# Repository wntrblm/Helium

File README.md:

# Winterbloom Helium

Helium is a precision buffered multiple and precision adder for Eurorack.

More details available at https://winterbloom.com/shop/helium

## Repository layout

This repository contains the hardware design files and user guide for Helium:

- **hardware/** contains the hardware design files for the mainboard and blank panel. These are all created using KiCAD.
- **user_guide/** contains the user's guide source files. These are written in Markdown and published using MkDocs.

## License and contributing

Helium is open-source hardware and software, however, licensing a project like this is a little complicated. Please take a chance to review the [LICENSE](LICENSE.md) file.

We welcome contributions! Please read our [Code of Conduct](CODE_OF_CONDUCT.md) first.

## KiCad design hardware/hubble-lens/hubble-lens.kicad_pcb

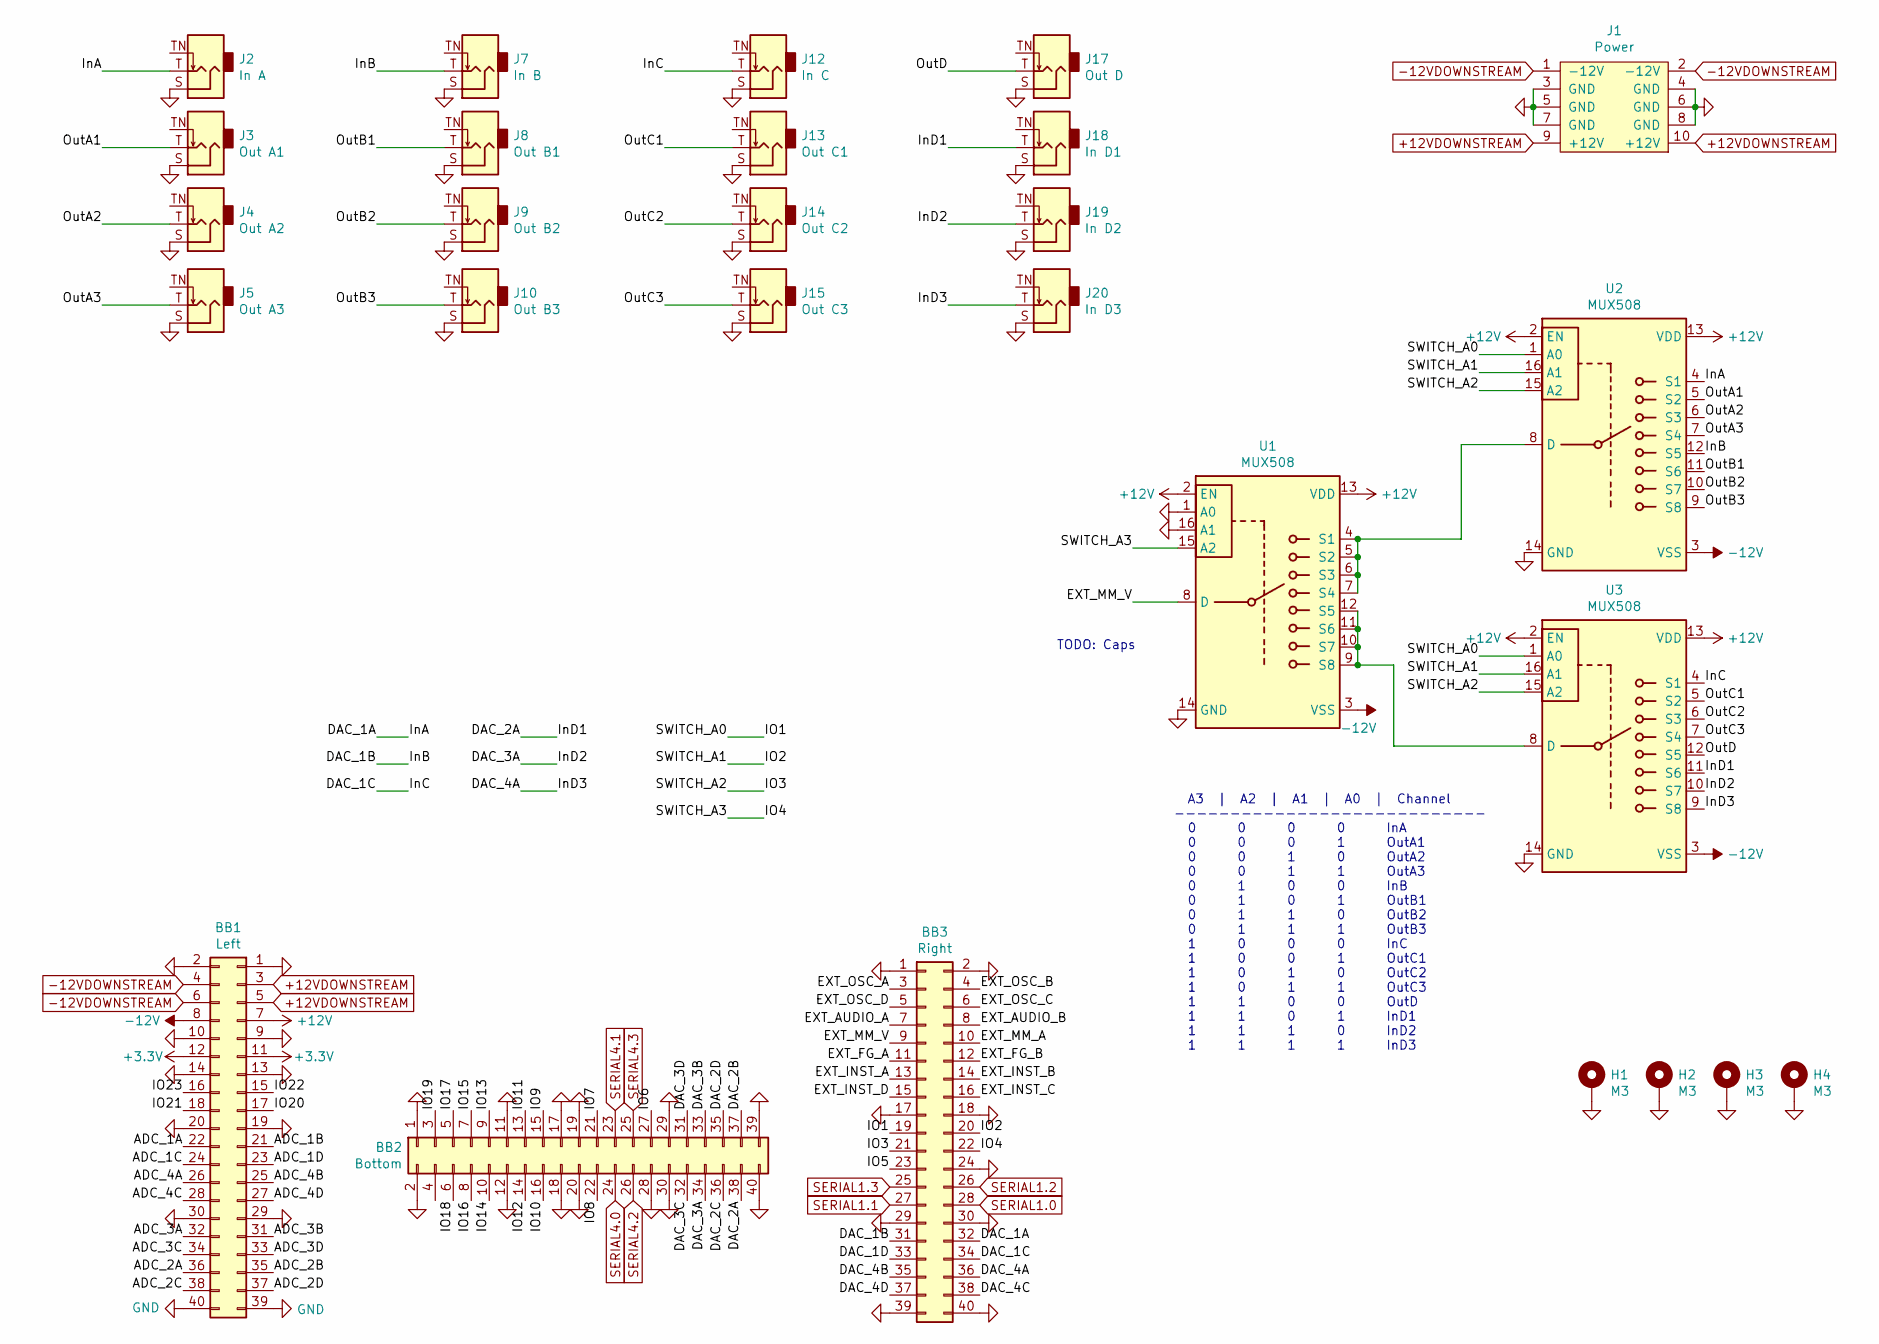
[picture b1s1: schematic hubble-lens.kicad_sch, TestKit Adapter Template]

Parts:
BB1: Left; PinSocket_2x20_P2.54mm_Vertical
BB2: Bottom; PinSocket_2x20_P2.54mm_Vertical
BB3: Right; PinSocket_2x20_P2.54mm_Vertical
H1, H2, H3, H4: M3; MountingHole_3.2mm_M3_Pad_Via
J1: Power; Eurorack_Power; mpn 302-S101
J2: In A; WQP-WQP518MA-skinny; mpn WQP-WQP518MA
J3: Out A1; WQP-WQP518MA-skinny; mpn WQP-WQP518MA
J4: Out A2; WQP-WQP518MA-skinny; mpn WQP-WQP518MA
J5: Out A3; WQP-WQP518MA-skinny; mpn WQP-WQP518MA
J7: In B; WQP-WQP518MA-skinny; mpn WQP-WQP518MA
J8: Out B1; WQP-WQP518MA-skinny; mpn WQP-WQP518MA
J9: Out B2; WQP-WQP518MA-skinny; mpn WQP-WQP518MA
J10: Out B3; WQP-WQP518MA-skinny; mpn WQP-WQP518MA
J12: In C; WQP-WQP518MA-skinny; mpn WQP-WQP518MA
J13: Out C1; WQP-WQP518MA-skinny; mpn WQP-WQP518MA
J14: Out C2; WQP-WQP518MA-skinny; mpn WQP-WQP518MA
J15: Out C3; WQP-WQP518MA-skinny; mpn WQP-WQP518MA
J17: Out D; WQP-WQP518MA-skinny; mpn WQP-WQP518MA
J18: In D1; WQP-WQP518MA-skinny; mpn WQP-WQP518MA
J19: In D2; WQP-WQP518MA-skinny; mpn WQP-WQP518MA
J20: In D3; WQP-WQP518MA-skinny; mpn WQP-WQP518MA
U1, U2, U3: MUX508; TSSOP-16_4.4x5mm_P0.65mm

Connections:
+3V3: BB1.11, BB1.12
+12V: BB1.7, U1.2 (EN), U1.13 (VDD), U2.2 (EN), U2.13 (VDD), U3.2 (EN), U3.13 (VDD)
+12VDOWNSTREAM: BB1.3, BB1.5, J1.9 (+12V), J1.10 (+12V)
-12V: BB1.8, U1.3 (VSS), U2.3 (VSS), U3.3 (VSS)
-12VDOWNSTREAM: BB1.4, BB1.6, J1.1 (-12V), J1.2 (-12V)
/ADC_1A: BB1.22
/ADC_1B: BB1.21
/ADC_1C: BB1.24
/ADC_1D: BB1.23
/ADC_2A: BB1.36
/ADC_2B: BB1.35
/ADC_2C: BB1.38
/ADC_2D: BB1.37
/ADC_3A: BB1.32
/ADC_3B: BB1.31
/ADC_3C: BB1.34
/ADC_3D: BB1.33
/ADC_4A: BB1.26
/ADC_4B: BB1.25
/ADC_4C: BB1.28
/ADC_4D: BB1.27
/DAC_1A: BB3.32, J2.T (Tip), U2.4 (S1)
/DAC_1B: BB3.31, J7.T (Tip), U2.12 (S5)
/DAC_1C: BB3.34, J12.T (Tip), U3.4 (S1)
/DAC_1D: BB3.33
/DAC_2A: BB2.38, J18.T (Tip), U3.11 (S6)
/DAC_2B: BB2.37
/DAC_2C: BB2.36
/DAC_2D: BB2.35
/DAC_3A: BB2.34, J19.T (Tip), U3.10 (S7)
/DAC_3B: BB2.33
/DAC_3C: BB2.32
/DAC_3D: BB2.31
/DAC_4A: BB3.36, J20.T (Tip), U3.9 (S8)
/DAC_4B: BB3.35
/DAC_4C: BB3.38
/DAC_4D: BB3.37
/EXT_AUDIO_A: BB3.7
/EXT_AUDIO_B: BB3.8
/EXT_FG_A: BB3.11
/EXT_FG_B: BB3.12
/EXT_INST_A: BB3.13
/EXT_INST_B: BB3.14
/EXT_INST_C: BB3.16
/EXT_INST_D: BB3.15
/EXT_MM_A: BB3.10
/EXT_MM_V: BB3.9, U1.8 (D)
/EXT_OSC_A: BB3.3
/EXT_OSC_B: BB3.4
/EXT_OSC_C: BB3.6
/EXT_OSC_D: BB3.5
/IO1: BB3.19, U2.1 (A0), U3.1 (A0)
/IO2: BB3.20, U2.16 (A1), U3.16 (A1)
/IO3: BB3.21, U2.15 (A2), U3.15 (A2)
/IO4: BB3.22, U1.15 (A2)
/IO5: BB3.23
/IO6: BB2.27
/IO7: BB2.21
/IO8: BB2.22
/IO9: BB2.15
/IO10: BB2.16
/IO11: BB2.13
/IO12: BB2.14
/IO13: BB2.9
/IO14: BB2.10
/IO15: BB2.7
/IO16: BB2.8
/IO17: BB2.5
/IO18: BB2.6
/IO19: BB2.3
/IO20: BB1.17
/IO21: BB1.18
/IO22: BB1.15
/IO23: BB1.16
/OutA1: J3.T (Tip), U2.5 (S2)
/OutA2: J4.T (Tip), U2.6 (S3)
/OutA3: J5.T (Tip), U2.7 (S4)
/OutB1: J8.T (Tip), U2.11 (S6)
/OutB2: J9.T (Tip), U2.10 (S7)
/OutB3: J10.T (Tip), U2.9 (S8)
/OutC1: J13.T (Tip), U3.5 (S2)
/OutC2: J14.T (Tip), U3.6 (S3)
/OutC3: J15.T (Tip), U3.7 (S4)
/OutD: J17.T (Tip), U3.12 (S5)
GND: BB1.1, BB1.2, BB1.9, BB1.10, BB1.13, BB1.14, BB1.19, BB1.20, BB1.29, BB1.30, BB1.39, BB1.40, BB2.1, BB2.2, BB2.11, BB2.12, BB2.17, BB2.18, BB2.19, BB2.20, BB2.28, BB2.29, BB2.30, BB2.39, BB2.40, BB3.1, BB3.2, BB3.17, BB3.18, BB3.24, BB3.29, BB3.30, BB3.39, BB3.40, H1.1, H2.1, H3.1, H4.1, J1.3 (GND), J1.4 (GND), J1.5 (GND), J1.6 (GND), J1.7 (GND), J1.8 (GND), J2.S (Sleeve), J3.S (Sleeve), J4.S (Sleeve), J5.S (Sleeve), J7.S (Sleeve), J8.S (Sleeve), J9.S (Sleeve), J10.S (Sleeve), J12.S (Sleeve), J13.S (Sleeve), J14.S (Sleeve), J15.S (Sleeve), J17.S (Sleeve), J18.S (Sleeve), J19.S (Sleeve), J20.S (Sleeve), U1.1 (A0), U1.14 (GND), U1.16 (A1), U2.14 (GND), U3.14 (GND)
unnamed: U1.4 (S1), U1.5 (S2), U1.6 (S3), U1.7 (S4), U2.8 (D)
unnamed: U1.9 (S8), U1.10 (S7), U1.11 (S6), U1.12 (S5), U3.8 (D)
SERIAL1.0: BB3.28
SERIAL1.1: BB3.27
SERIAL1.2: BB3.26
SERIAL1.3: BB3.25
SERIAL4.0: BB2.24
SERIAL4.1: BB2.23
SERIAL4.2: BB2.26
SERIAL4.3: BB2.25

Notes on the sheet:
A3 | A2 | A1 | A0 | Channel ---------------------------- 0 0 0 0 InA 0 0 0 1 OutA1 0 0 1 0 OutA2 0 0 1 1 OutA3 0 1 0 0 InB 0 1 0 1 OutB1 0 1 1 0 OutB2 0 1 1 1 OutB3 1 0 0 0 InC 1 0 0 1 OutC1 1 0 1 0 OutC2 1 0 1 1 OutC3 1 1 0 0 OutD 1 1 0 1 InD1 1 1 1 0 InD2 1 1 1 1 InD3
TODO: Caps

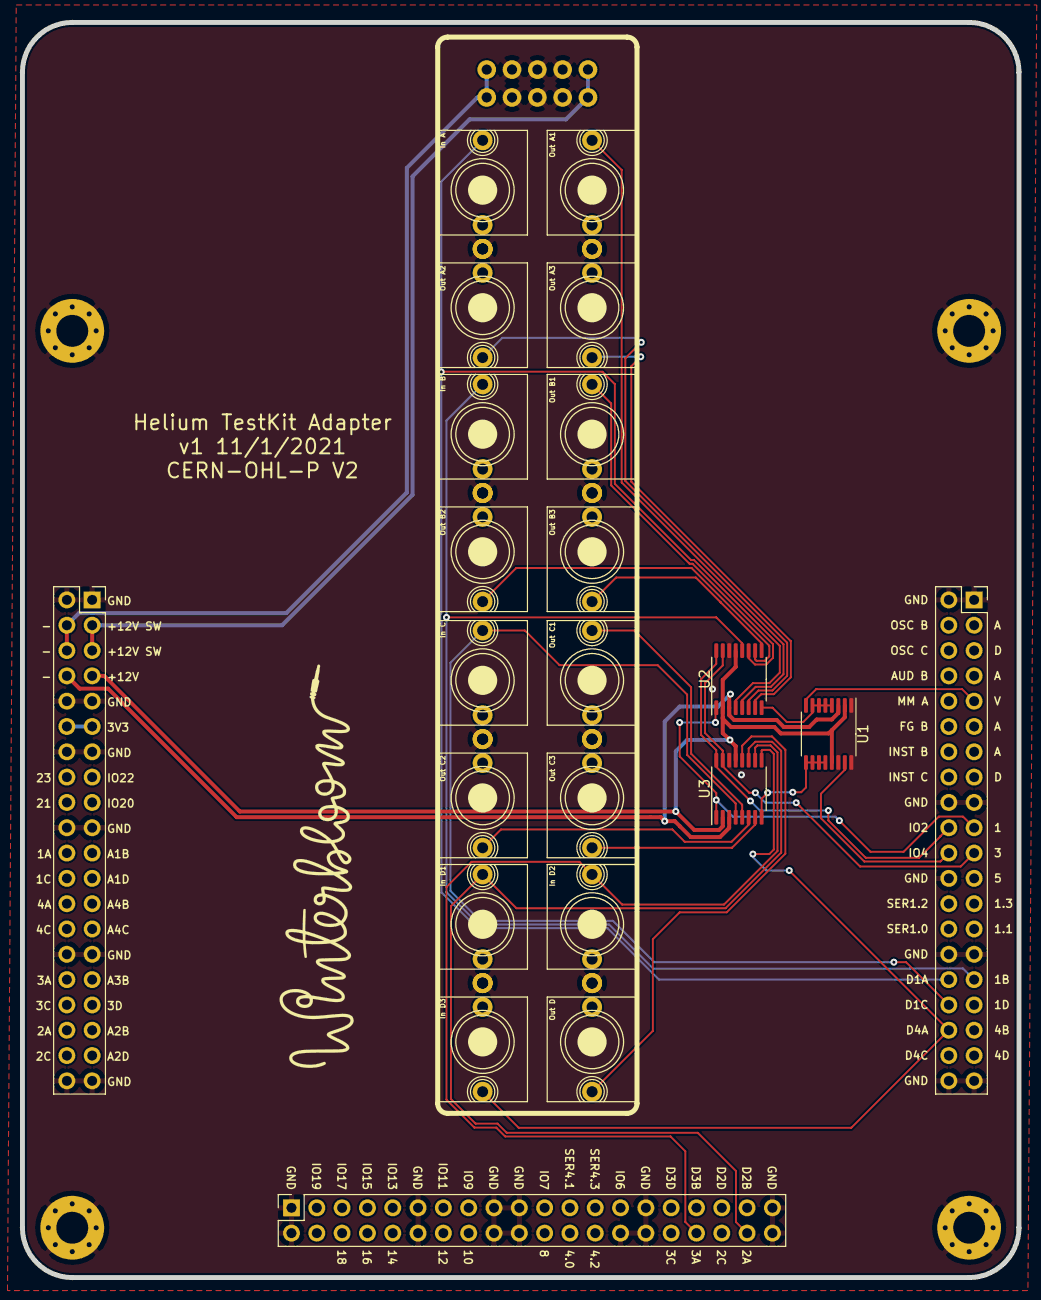
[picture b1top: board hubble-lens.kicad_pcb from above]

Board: 2 copper layers, 100.0 x 126.0 mm, 27 parts (1 on the bottom side), 29 nets.

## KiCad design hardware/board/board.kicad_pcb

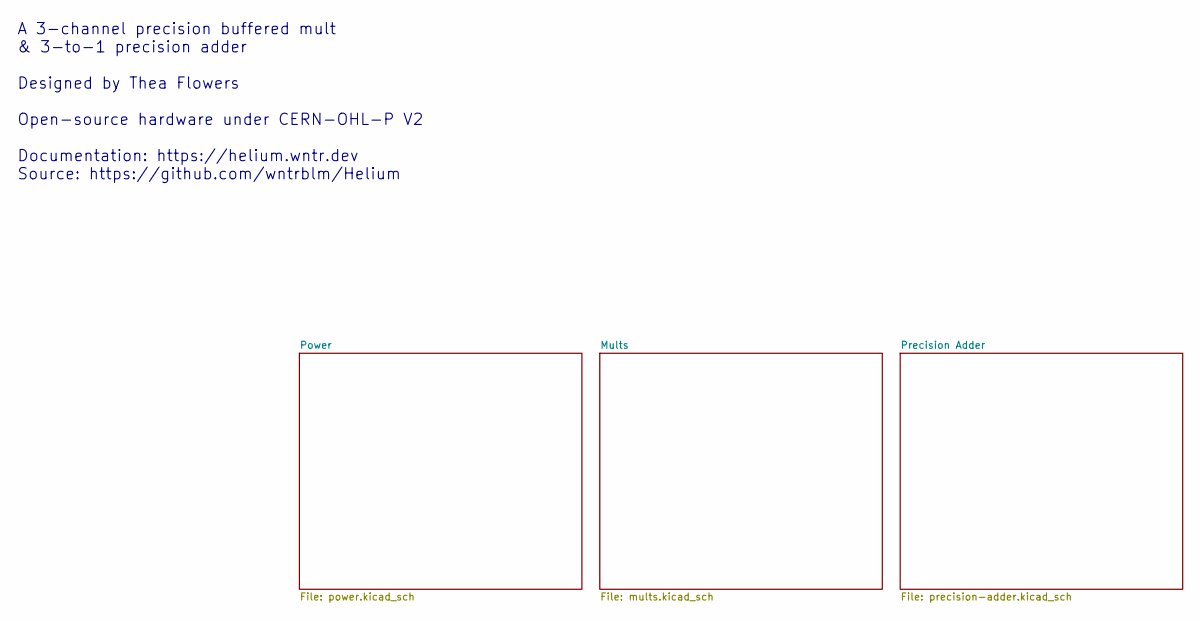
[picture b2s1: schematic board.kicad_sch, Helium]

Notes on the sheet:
A 3-channel precision buffered mult & 3-to-1 precision adder Designed by Thea Flowers Open-source hardware under CERN-OHL-P V2 Documentation: https://helium.wntr.dev Source: https://github.com/wntrblm/Helium

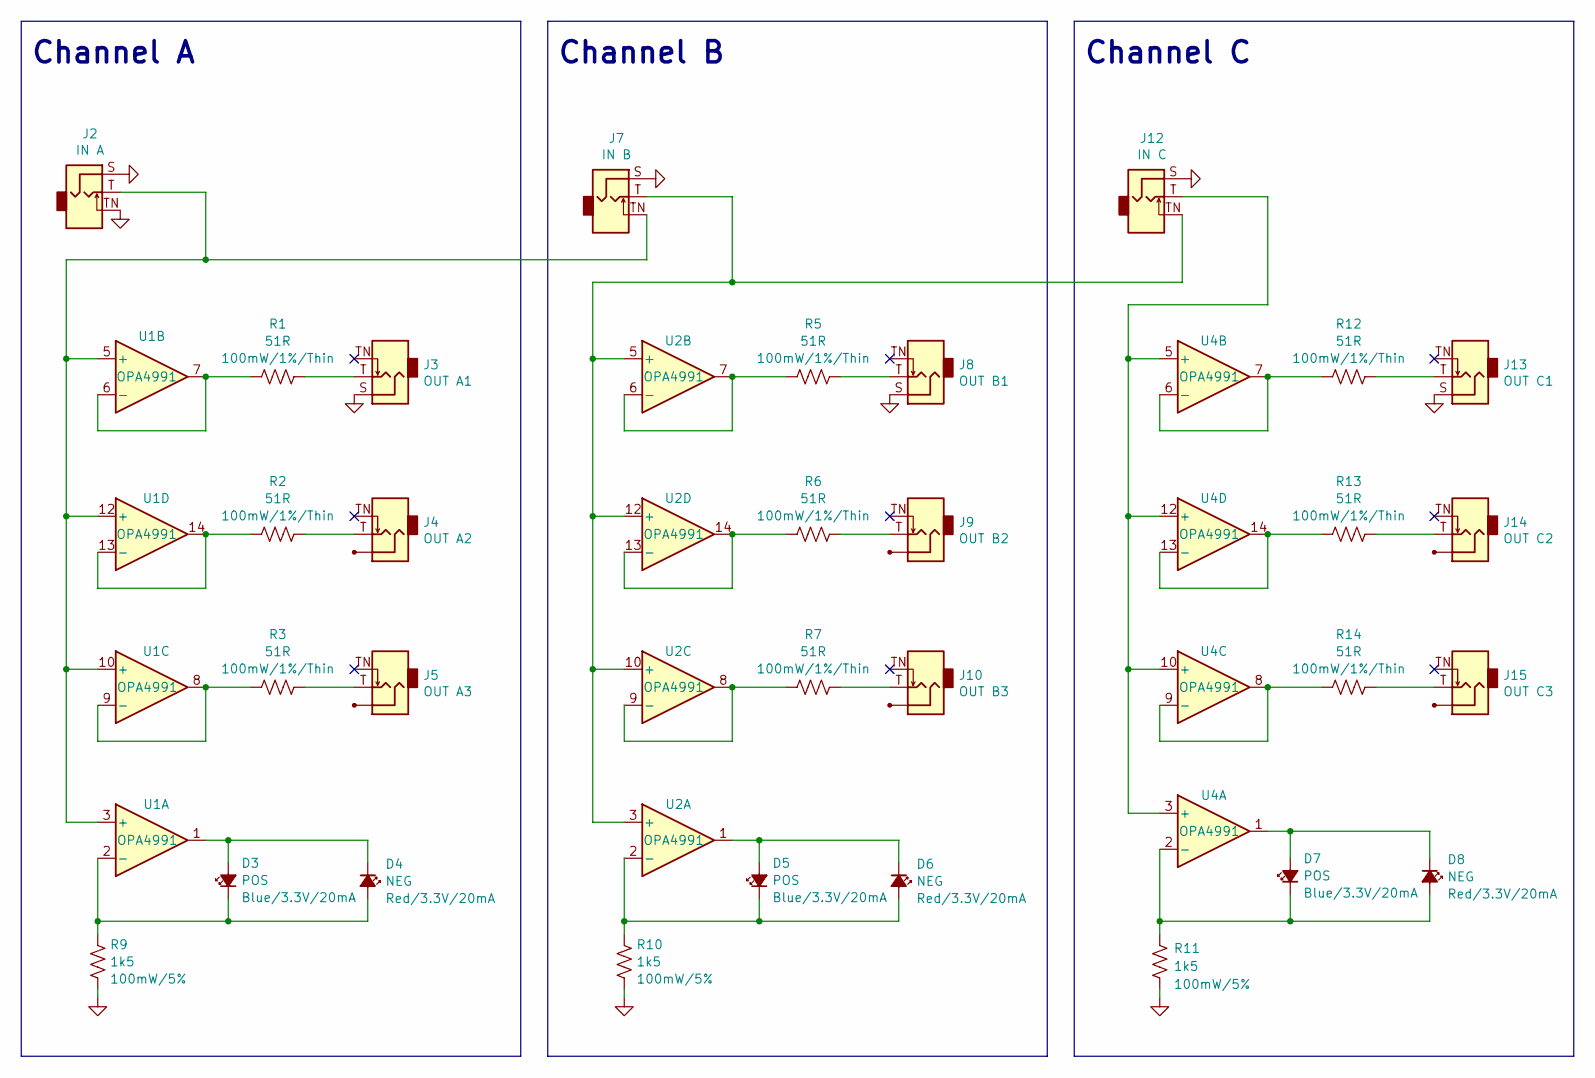
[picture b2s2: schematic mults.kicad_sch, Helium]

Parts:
D3, D5, D7: POS; LED_0805_Kingbright_APT2012; Rating Blue/3.3V/20mA; MPN APT2012VBC/D; DigiKey 754-1794-1-ND
D4, D6, D8: NEG; LED_0805_Kingbright_APT2012; Rating Red/3.3V/20mA; MPN APT2012SURCK; DigiKey 754-1133-1-ND
J2: IN A; AudioJack_WQP518MA_Compact_S; MPN WQP-WQP518MA
J3: OUT A1; AudioJack_WQP518MA_Compact_S; MPN WQP-WQP518MA
J4: OUT A2; AudioJack_WQP518MA_No_S; MPN WQP-WQP518MA
J5: OUT A3; AudioJack_WQP518MA_No_S; MPN WQP-WQP518MA
J7: IN B; AudioJack_WQP518MA_Compact_S; MPN WQP-WQP518MA
J8: OUT B1; AudioJack_WQP518MA_Compact_S; MPN WQP-WQP518MA
J9: OUT B2; AudioJack_WQP518MA_No_S; MPN WQP-WQP518MA
J10: OUT B3; AudioJack_WQP518MA_No_S; MPN WQP-WQP518MA
J12: IN C; AudioJack_WQP518MA_Compact_S; MPN WQP-WQP518MA
J13: OUT C1; AudioJack_WQP518MA_Compact_S; MPN WQP-WQP518MA
J14: OUT C2; AudioJack_WQP518MA_No_S; MPN WQP-WQP518MA
J15: OUT C3; AudioJack_WQP518MA_No_S; MPN WQP-WQP518MA
R1, R2, R3, R5, R6, R7, R12, R13, R14: 51R; R_0603_HandSolder; Rating 100mW/1%/Thin; MPN RT0603FRE0751RL; DigiKey 13-RT0603FRE0751RLCT-ND
R9, R10, R11: 1k5; R_0603_HandSolder; Rating 100mW/5%; MPN RC0603JR-071K5L; DigiKey 311-1.5KGRCT-ND
U1, U2, U4: OPA4991; TSSOP-14_4.4x5mm_P0.65mm; MPN OPA4991IPWR; DigiKey 296-OPA4991IPWRCT-ND

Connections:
GND: J2.S (Sleeve), J2.TN (Tip_normalize), J3.S (Sleeve), J7.S (Sleeve), J8.S (Sleeve), J12.S (Sleeve), J13.S (Sleeve), R9.1, R10.1, R11.1; also elsewhere on the board
unnamed: D3.2 (A), D4.1 (K), U1.1
unnamed: D3.1 (K), D4.2 (A), R9.2, U1.2 (-)
unnamed: D5.2 (A), D6.1 (K), U2.1
unnamed: D5.1 (K), D6.2 (A), R10.2, U2.2 (-)
unnamed: D7.2 (A), D8.1 (K), U4.1
unnamed: D7.1 (K), D8.2 (A), R11.2, U4.2 (-)
unnamed: J2.T (Tip), J7.TN (Tip_normalize), U1.3 (+), U1.5 (+), U1.10 (+), U1.12 (+)
unnamed: J3.T (Tip), R1.1
unnamed: J4.T (Tip), R2.1
unnamed: J5.T (Tip), R3.1
unnamed: J8.T (Tip), R5.1
unnamed: J9.T (Tip), R6.1
unnamed: J10.T (Tip), R7.1
unnamed: J12.T (Tip), U4.3 (+), U4.5 (+), U4.10 (+), U4.12 (+)
unnamed: J7.T (Tip), J12.TN (Tip_normalize), U2.3 (+), U2.5 (+), U2.10 (+), U2.12 (+)
unnamed: J13.T (Tip), R12.1
unnamed: J14.T (Tip), R13.1
unnamed: J15.T (Tip), R14.1
unnamed: R1.2, U1.6 (-), U1.7
unnamed: R3.2, U1.8, U1.9 (-)
unnamed: R2.2, U1.13 (-), U1.14
unnamed: R5.2, U2.6 (-), U2.7
unnamed: R7.2, U2.8, U2.9 (-)
unnamed: R6.2, U2.13 (-), U2.14
unnamed: R12.2, U4.6 (-), U4.7
unnamed: R14.2, U4.8, U4.9 (-)
unnamed: R13.2, U4.13 (-), U4.14

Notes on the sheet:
Channel C
Channel B
Channel A

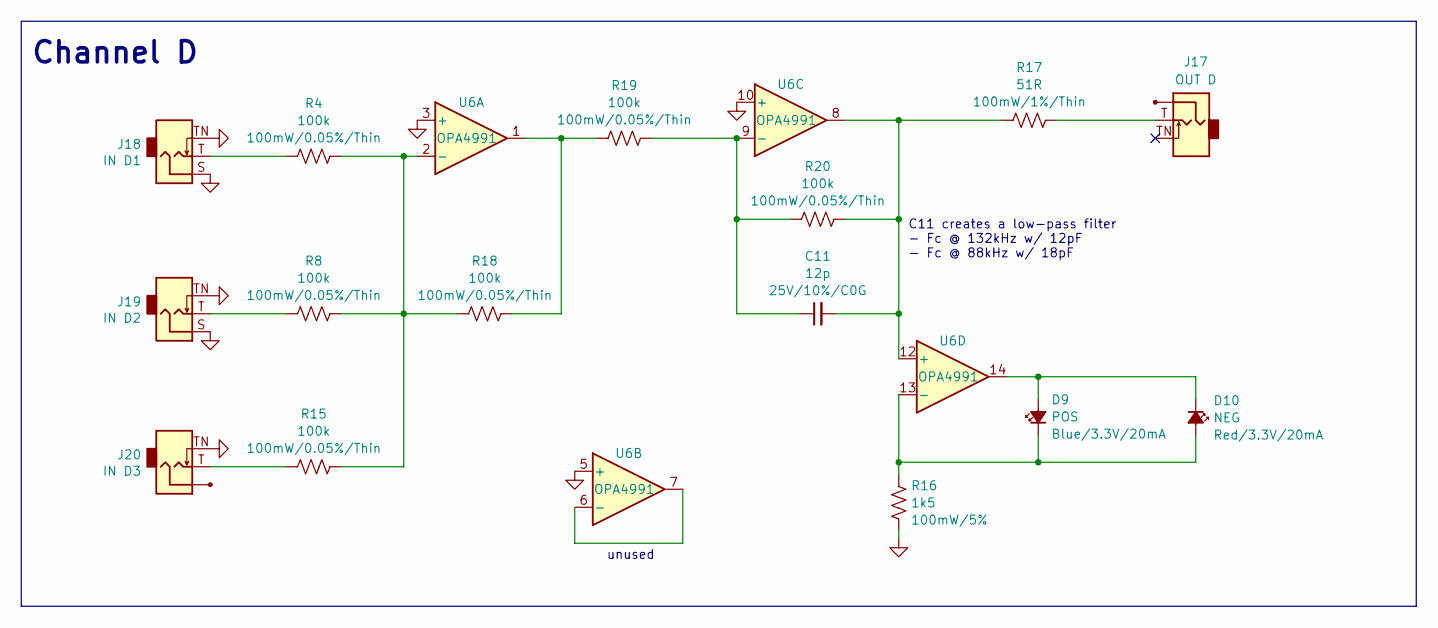
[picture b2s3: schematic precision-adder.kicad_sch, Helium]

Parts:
C11: 12p; C_0603_HandSolder; Rating 25V/10%/C0G; MPN CC0603JPNPO9BN120; DigiKey 13-CC0603JPNPO9BN120CT-ND
D9: POS; LED_0805_Kingbright_APT2012; Rating Blue/3.3V/20mA; MPN APT2012VBC/D; DigiKey 754-1794-1-ND
D10: NEG; LED_0805_Kingbright_APT2012; Rating Red/3.3V/20mA; MPN APT2012SURCK; DigiKey 754-1133-1-ND
J17: OUT D; AudioJack_WQP518MA_No_S; MPN WQP-WQP518MA
J18: IN D1; AudioJack_WQP518MA_Compact_S; MPN WQP-WQP518MA
J19: IN D2; AudioJack_WQP518MA_Compact_S; MPN WQP-WQP518MA
J20: IN D3; AudioJack_WQP518MA_No_S; MPN WQP-WQP518MA
R4, R8, R15, R18, R19, R20: 100k; R_0603_HandSolder; Rating 100mW/0.05%/Thin; MPN RG1608N-104-W-T1; DigiKey RG16N100KWCT-ND
R16: 1k5; R_0603_HandSolder; Rating 100mW/5%; MPN RC0603JR-071K5L; DigiKey 311-1.5KGRCT-ND
R17: 51R; R_0603_HandSolder; Rating 100mW/1%/Thin; MPN RT0603FRE0751RL; DigiKey 13-RT0603FRE0751RLCT-ND
U6: OPA4991; TSSOP-14_4.4x5mm_P0.65mm; MPN OPA4991IPWR; DigiKey 296-OPA4991IPWRCT-ND

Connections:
GND: J18.S (Sleeve), J18.TN (Tip_normalize), J19.S (Sleeve), J19.TN (Tip_normalize), J20.TN (Tip_normalize), R16.1, U6.3 (+), U6.5 (+), U6.10 (+); also elsewhere on the board
unnamed: D9.1 (K), D10.2 (A), R16.2, U6.13 (-)
unnamed: D9.2 (A), D10.1 (K), U6.14
unnamed: J17.T (Tip), R17.1
unnamed: J18.T (Tip), R4.2
unnamed: J19.T (Tip), R8.2
unnamed: J20.T (Tip), R15.2
unnamed: R18.1, R19.2, U6.1
unnamed: R4.1, R8.1, R15.1, R18.2, U6.2 (-)
unnamed: U6.6 (-), U6.7
unnamed: C11.1, R19.1, R20.2, U6.9 (-)
unnamed: C11.2, R17.2, R20.1, U6.8, U6.12 (+)

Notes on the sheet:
unused
C11 creates a low-pass filter - Fc @ 132kHz w/ 12pF - Fc @ 88kHz w/ 18pF
Channel D

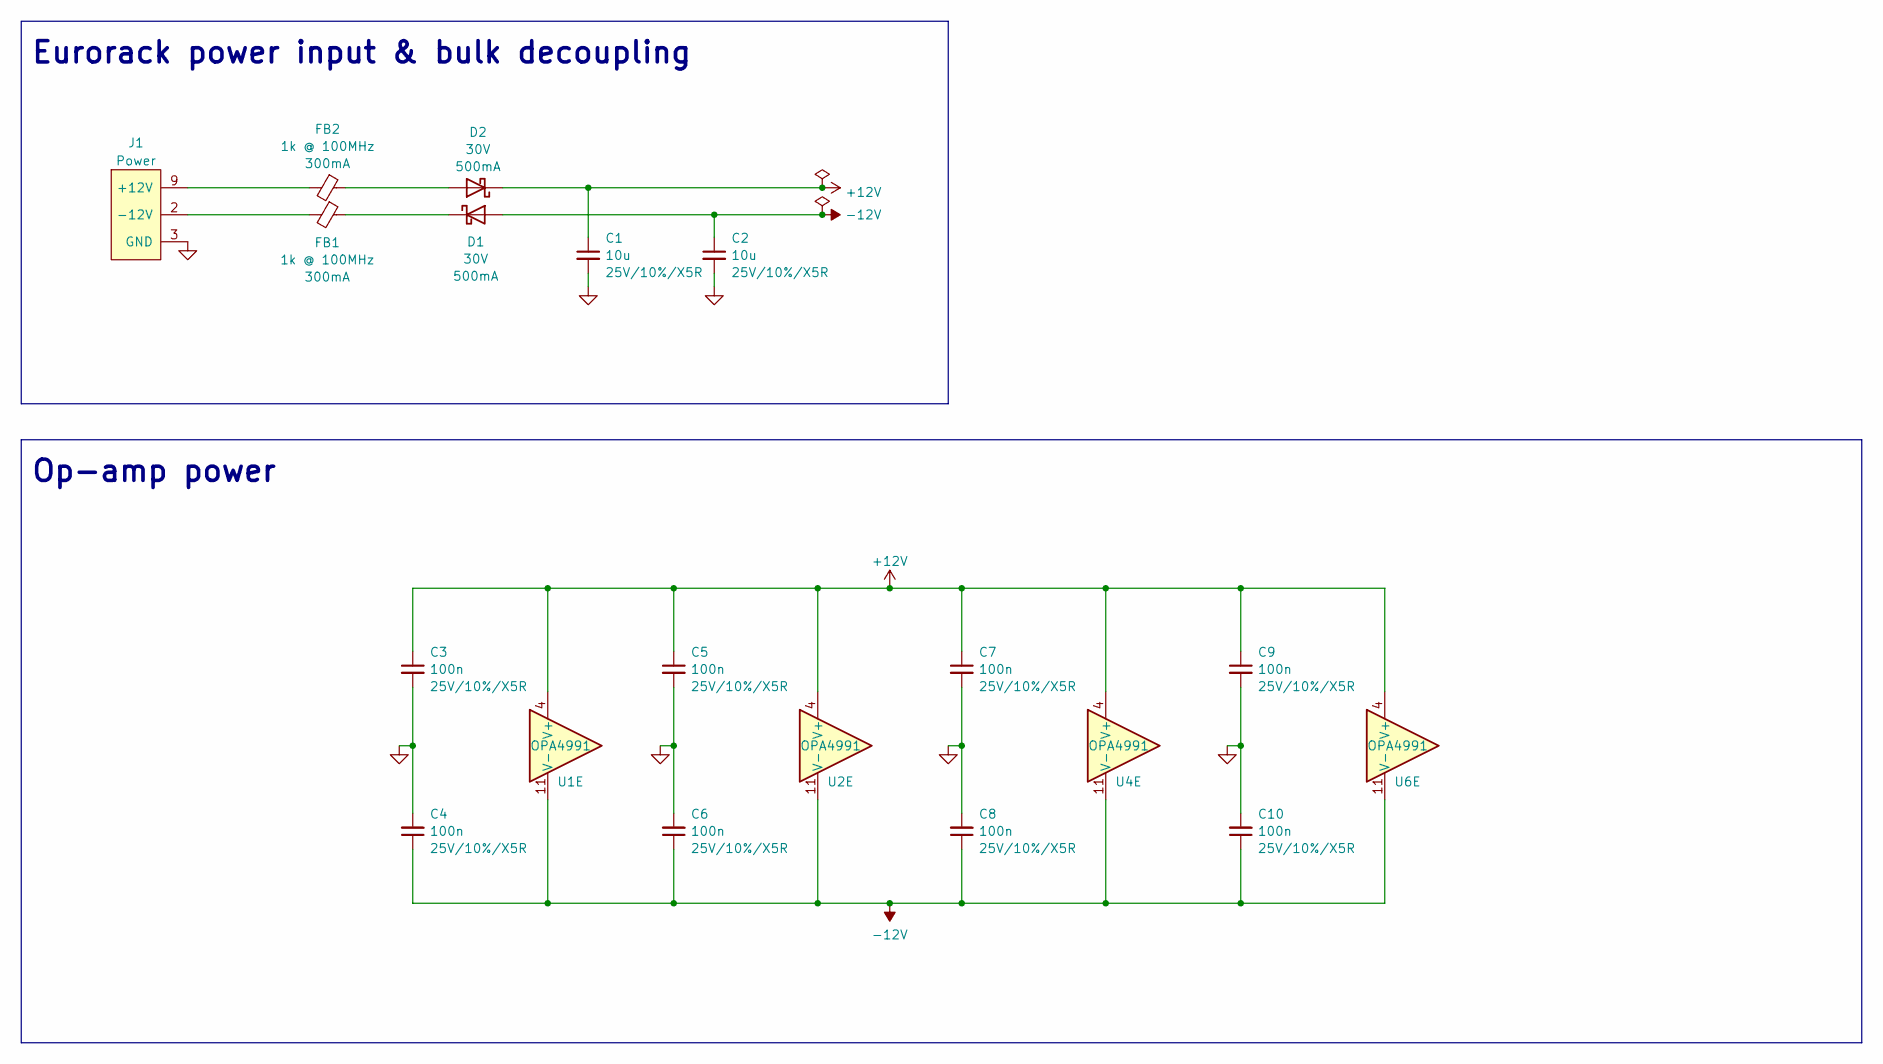
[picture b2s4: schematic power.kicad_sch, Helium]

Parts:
C1, C2: 10u; C_0805_HandSolder; Rating 25V/10%/X5R; MPN GRM21BR61E106KA73K; DigiKey 490-16824-1-ND
C3, C4, C5, C6, C7, C8, C9, C10: 100n; C_0603_HandSolder; Rating 25V/10%/X5R; MPN CL10B104KB8NNNC; DigiKey 1276-1000-2-ND
D1, D2: 30V; D_SOD-123+SOD-123F; Rating 500mA; MPN PMEG2005EGWX; DigiKey 1727-7329-1-ND
FB1, FB2: 1k @ 100MHz; L_0603_HandSolder; Rating 300mA; MPN BLM18AG102SN1D; DigiKey 490-1015-1-ND
J1: Power; Eurorack_Power_2x5_Shrouded_Lock; MPN 302-S101; DigiKey ED1543-ND
U1, U2, U4, U6: OPA4991; TSSOP-14_4.4x5mm_P0.65mm; MPN OPA4991IPWR; DigiKey 296-OPA4991IPWRCT-ND

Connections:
+12V: C1.1, C3.1, C5.1, C7.1, C9.1, D2.1 (K), U1.4 (V+), U2.4 (V+), U4.4 (V+), U6.4 (V+)
-12V: C2.1, C4.1, C6.1, C8.1, C10.1, D1.2 (A), U1.11 (V-), U2.11 (V-), U4.11 (V-), U6.11 (V-)
GND: C1.2, C2.2, C3.2, C4.2, C5.2, C6.2, C7.2, C8.2, C9.2, C10.2, J1.3 (GND), J1.4 (GND), J1.5 (GND), J1.6 (GND), J1.7 (GND), J1.8 (GND); also elsewhere on the board
unnamed: D1.1 (K), FB1.1
unnamed: D2.2 (A), FB2.1
unnamed: FB1.2, J1.1 (-12V), J1.2 (-12V)
unnamed: FB2.2, J1.9 (+12V), J1.10 (+12V)

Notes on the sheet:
Eurorack power input & bulk decoupling
Op-amp power

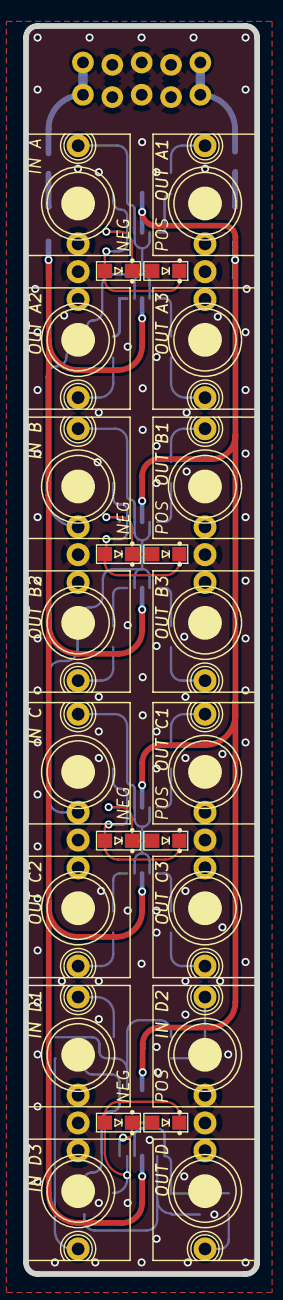
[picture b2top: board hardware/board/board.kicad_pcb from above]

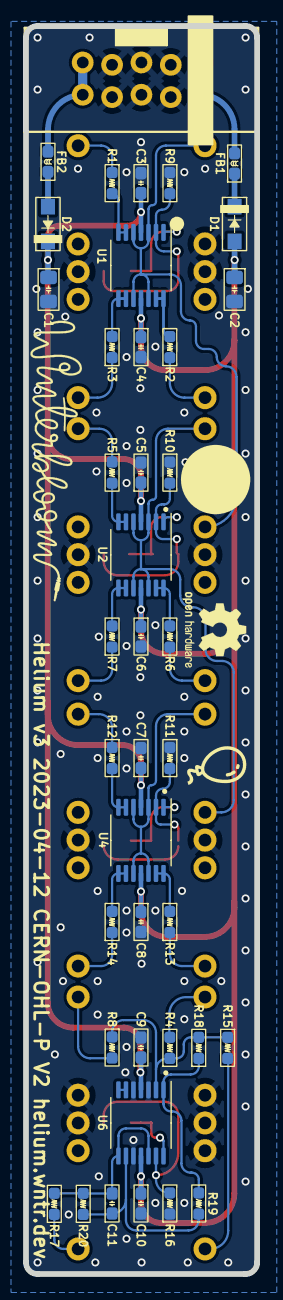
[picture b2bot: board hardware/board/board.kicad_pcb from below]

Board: 2 copper layers, 20.0 x 108.0 mm, 64 parts (40 on the bottom side), 45 nets.

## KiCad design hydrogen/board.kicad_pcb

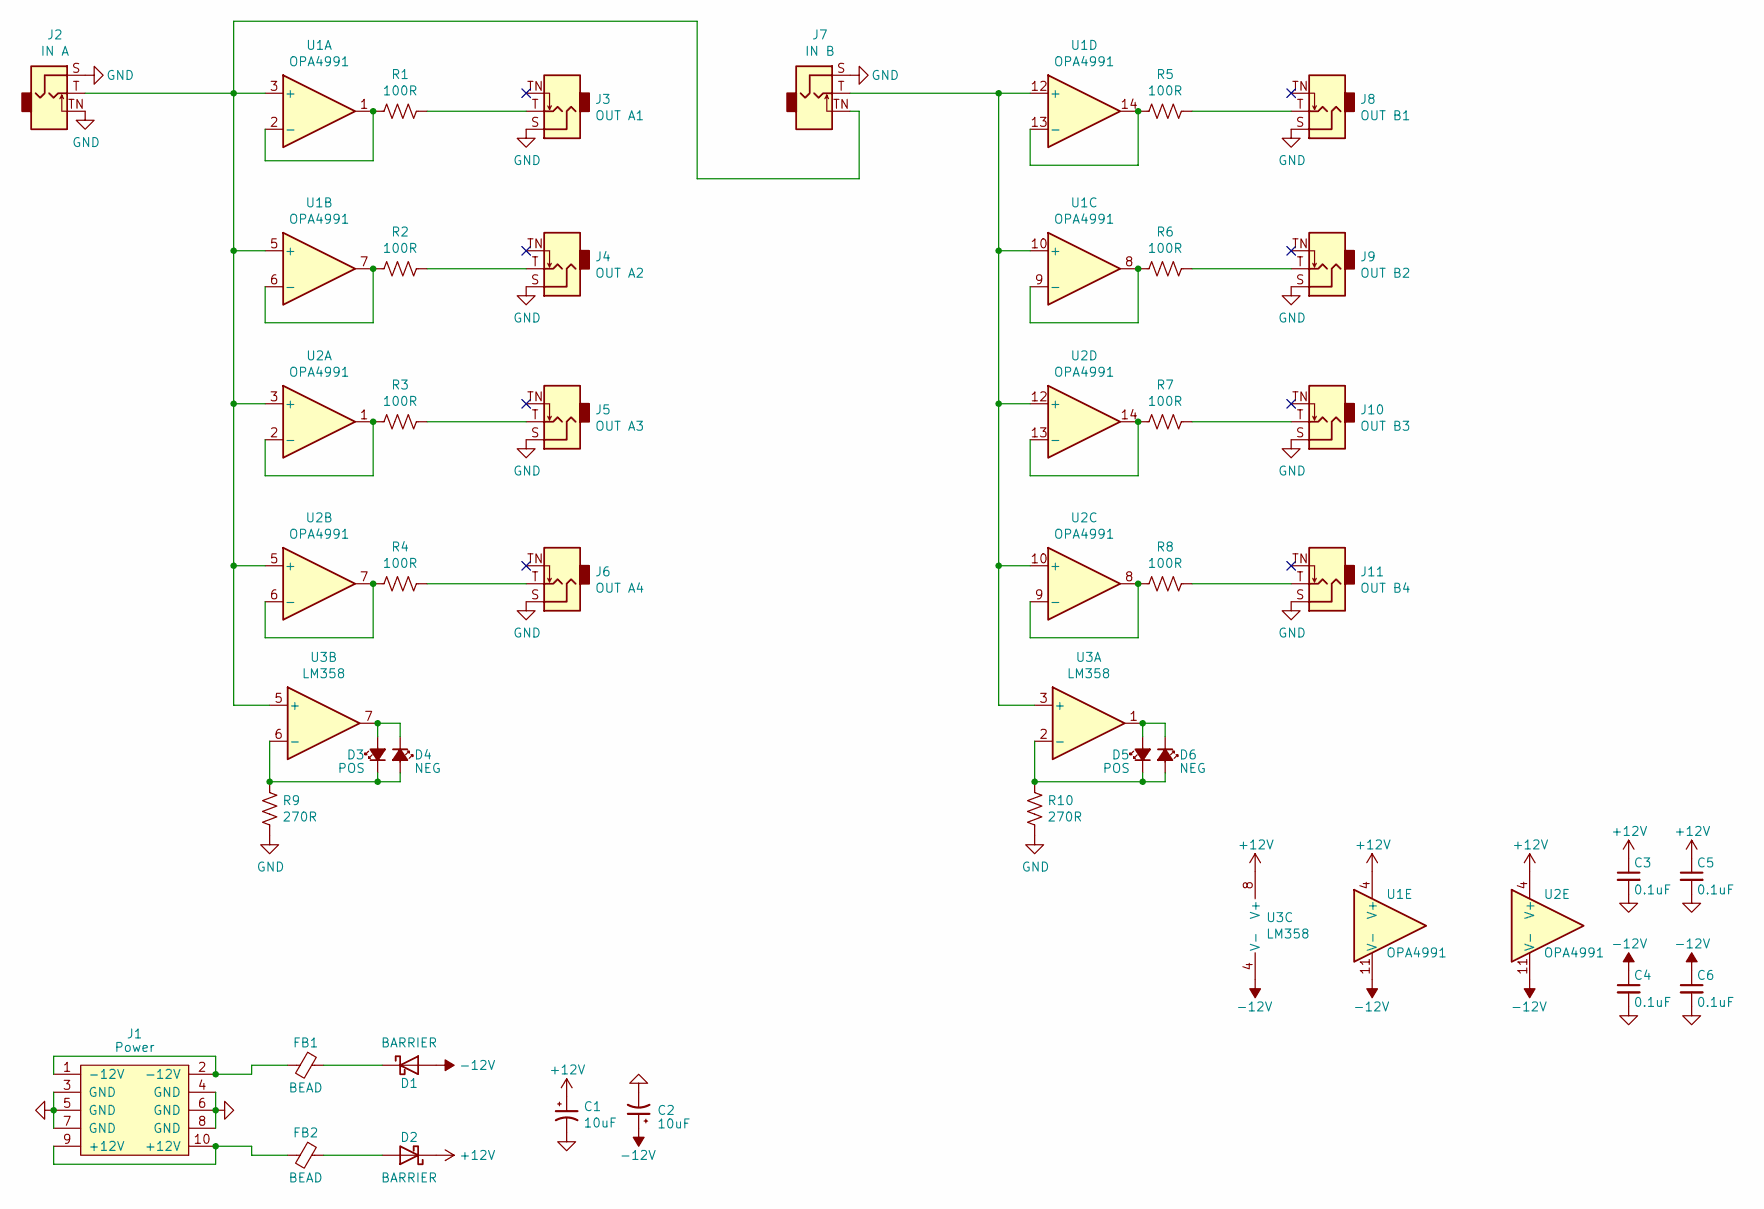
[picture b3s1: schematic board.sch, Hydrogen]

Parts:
C1, C2: 10uF; C_0805_2012Metric_Pad1.18x1.45mm_HandSolder; mpn GRM21BR61E106KA73K
C3, C4, C5, C6: 0.1uF; C_0603_1608Metric_Pad1.08x0.95mm_HandSolder; mpn C1608X7R1E104K080AA
D1, D2: BARRIER; DIODE_SOD-123_SOD-123F; mpn PMEG2005EGWX
D3, D5: POS; LED_0805_Kingbright_APT2012; mpn APT2012VBC/D
D4, D6: NEG; LED_0805_Kingbright_APT2012; mpn APT2012SURCK
FB1, FB2: BEAD; L_0603_1608Metric_Pad1.05x0.95mm_HandSolder; mpn 742792664
J1: Power; Eurorack_Power; mpn 302-S101
J2: IN A; WQP-WQP518MA-skinny; mpn WQP-WQP518MA
J3: OUT A1; WQP-WQP518MA-skinny; mpn WQP-WQP518MA
J4: OUT A2; WQP-WQP518MA-skinny; mpn WQP-WQP518MA
J5: OUT A3; WQP-WQP518MA-skinny; mpn WQP-WQP518MA
J6: OUT A4; WQP-WQP518MA-skinny; mpn WQP-WQP518MA
J7: IN B; WQP-WQP518MA-skinny; mpn WQP-WQP518MA
J8: OUT B1; WQP-WQP518MA-skinny; mpn WQP-WQP518MA
J9: OUT B2; WQP-WQP518MA-skinny; mpn WQP-WQP518MA
J10: OUT B3; WQP-WQP518MA-skinny; mpn WQP-WQP518MA
J11: OUT B4; WQP-WQP518MA-skinny; mpn WQP-WQP518MA
R1, R2, R3, R4, R5, R6, R7, R8: 100R; R_0603_1608Metric_Pad0.98x0.95mm_HandSolder; mpn R0816P-101-D
R9, R10: 270R; R_0603_1608Metric_Pad0.98x0.95mm_HandSolder; mpn ERJ-3GEYJ271V
U1, U2: OPA4991; TSSOP-14_4.4x5mm_P0.65mm; mpn OPA4991IPWR
U3: LM358; TSSOP-8_4.4x3mm_P0.65mm; mpn LM358PWR

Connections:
+12V: C1.1, C3.1, C5.1, D2.1 (K), U1.4 (V+), U2.4 (V+), U3.8 (V+)
-12V: C2.1, C4.1, C6.1, D1.2 (A), U1.11 (V-), U2.11 (V-), U3.4 (V-)
GND: C1.2, C2.2, C3.2, C4.2, C5.2, C6.2, J1.3 (GND), J1.4 (GND), J1.5 (GND), J1.6 (GND), J1.7 (GND), J1.8 (GND), J2.S (Sleeve), J2.TN (Tip_normalize), J3.S (Sleeve), J4.S (Sleeve), J5.S (Sleeve), J6.S (Sleeve), J7.S (Sleeve), J8.S (Sleeve), J9.S (Sleeve), J10.S (Sleeve), J11.S (Sleeve), R9.1, R10.1
unnamed: D1.1 (K), FB1.1
unnamed: D2.2 (A), FB2.1
unnamed: D3.1 (K), D4.2 (A), R9.2, U3.6 (-)
unnamed: D3.2 (A), D4.1 (K), U3.7
unnamed: D5.1 (K), D6.2 (A), R10.2, U3.2 (-)
unnamed: D5.2 (A), D6.1 (K), U3.1
unnamed: FB1.2, J1.1 (-12V), J1.2 (-12V)
unnamed: FB2.2, J1.9 (+12V), J1.10 (+12V)
unnamed: J2.T (Tip), J7.TN (Tip_normalize), U1.3 (+), U1.5 (+), U2.3 (+), U2.5 (+), U3.5 (+)
unnamed: J3.T (Tip), R1.1
unnamed: J4.T (Tip), R2.1
unnamed: J5.T (Tip), R3.1
unnamed: J6.T (Tip), R4.1
unnamed: J7.T (Tip), U1.10 (+), U1.12 (+), U2.10 (+), U2.12 (+), U3.3 (+)
unnamed: J8.T (Tip), R5.1
unnamed: J9.T (Tip), R6.1
unnamed: J10.T (Tip), R7.1
unnamed: J11.T (Tip), R8.1
unnamed: R1.2, U1.1, U1.2 (-)
unnamed: R2.2, U1.6 (-), U1.7
unnamed: R3.2, U2.1, U2.2 (-)
unnamed: R4.2, U2.6 (-), U2.7
unnamed: R5.2, U1.13 (-), U1.14
unnamed: R6.2, U1.8, U1.9 (-)
unnamed: R7.2, U2.13 (-), U2.14
unnamed: R8.2, U2.8, U2.9 (-)

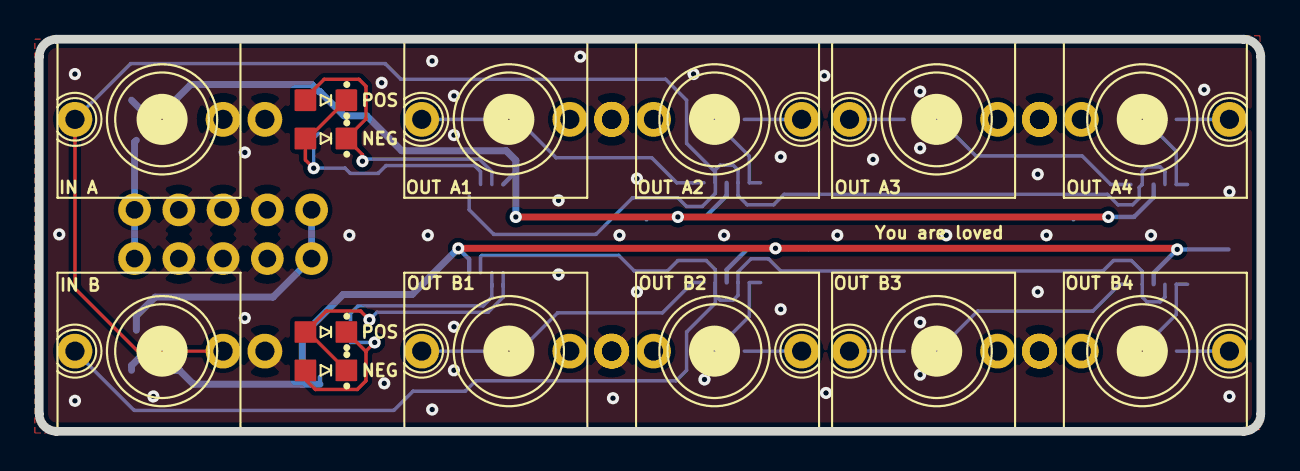
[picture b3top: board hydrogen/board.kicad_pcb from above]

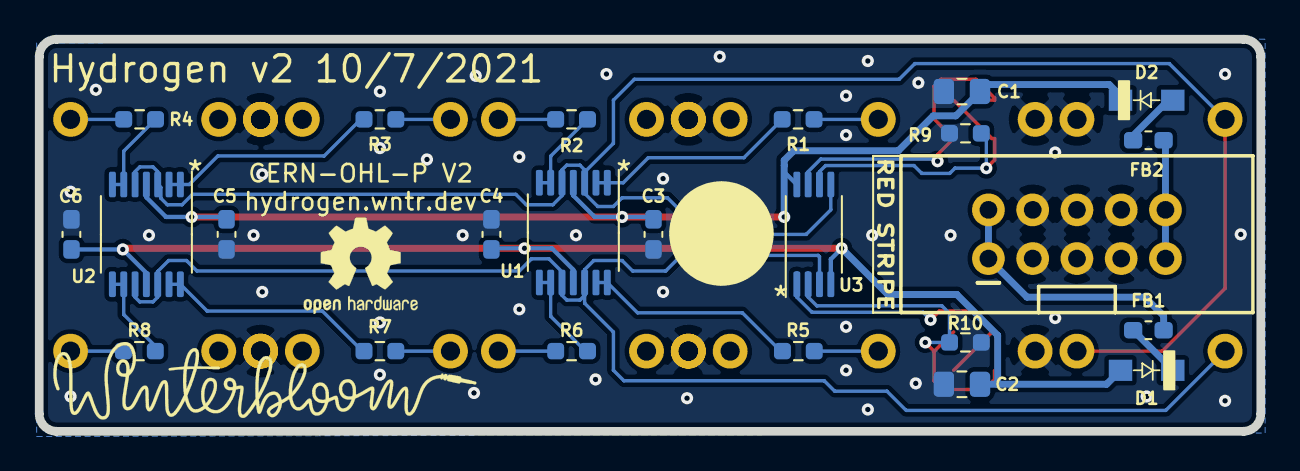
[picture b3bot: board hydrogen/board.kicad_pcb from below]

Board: 2 copper layers, 70.1 x 22.5 mm, 38 parts (24 on the bottom side), 29 nets.

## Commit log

2021-09-21 Initial versions
2021-10-03 Changes from tests on first revision
    1. Silkscreen legibility changes
    2. Added version numbers and such to page info blocks
    3. Change MPNs and values
    4. Change footprints for LEDs and Diodes.
    5. Pin one markers
2021-10-08 Rename folders
2021-10-08 Fix Hydrogen's page size
2021-10-08 Fix Helium's page size
2021-10-08 Add circle for QA sticker to Helium
2021-10-08 Add circle for QA sticker to Hydrogen
2021-10-10 Make trans rights bigger
2021-10-26 Update hydrogen
2021-11-08 Remove hydrogen files
2021-11-08 Move board design into hardware/
2021-11-08 Add testkit adapter
2021-11-08 Move .gitignore into hardware/
2021-11-08 Add readme, license, etc.
2021-11-08 Update resistor values; create PDF
2021-11-08 Add user guide
2021-11-16 Update values for resistors
2021-11-16 Update specs in user guide
2021-12-08 hardware: add laser design's for the testkit adapter board guide, pin holder, and pressure plate
2021-12-25 user guide: Add surface mount kit assembly guide
2021-12-28 hardware: convert to KiCAD 6, fix C2
2021-12-28 hardware: update PDF of schematic
2021-12-30 user guide: finish up manual
2022-01-08 user guide: Add kit assembly guide
2022-01-09 user guide: Fix typo from Hydrogen to Helium
2022-01-11 s/hydrogen/helium
2022-01-11 Add factory test script
2022-01-25 hardware: update page layout to Winterbloom's standard layout
2022-02-03 factory: move main script into if __main__ block
2022-02-03 user guide: Add oshw certification
2022-02-03 meta: automatically publish user guide when changes are pushed
2022-06-19 user guide: link to assembled and kit product pages
2022-06-19 Deployed ac2cdcd with MkDocs version: 1.3.0
2023-02-26 Update KiCAD project to V7
2023-04-13 hardware: revision 3
    - Update to new Winterbloom footprints
    - Update to match current Winterbloom design standards
    - Re-route traces
    - Update legends
2023-06-25 hardware: set drill origin
2023-06-29 factory: fix channel B measurements, modify acceptable results slightly based on real-world data
2023-07-24 user guide: remove screws and power cable from kit contents
2023-11-27 hardware: Add faceplate design
2023-11-27 hardware: Changes for self-sourcing
    - Add manufacturer part numbers and DigiKey, Mouser, and LCSC part numbers for all BOM items.
    - Split schematic into multiple US letter-sized sheets.
    - Update to new Winterbloom drawing sheet.
    - Create new PDF of schematic.
    - Create gerbers.zip with pre-made Gerbers.
2023-11-27 user guide: Add self-source guide
2023-11-27 hardware: rename testkit-adapter to hubble-lens
2024-02-06 user guide: switch to Wintersong theme, replace illustrations with svgs
2024-02-06 meta: update docs build dependencies and docs github action
2024-02-23 user guide: you don't actually need a smol screwdriver to build this
2024-02-23 Deployed f989ab2 with MkDocs version: 1.5.3
2024-06-16 factory: adjust how standard deviation is calculated and checked
2025-04-18 Deployed 1cecf97 with MkDocs version: 1.6.1
